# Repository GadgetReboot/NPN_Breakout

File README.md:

# NPN_Breakout
NPN Transistor Breakout Board

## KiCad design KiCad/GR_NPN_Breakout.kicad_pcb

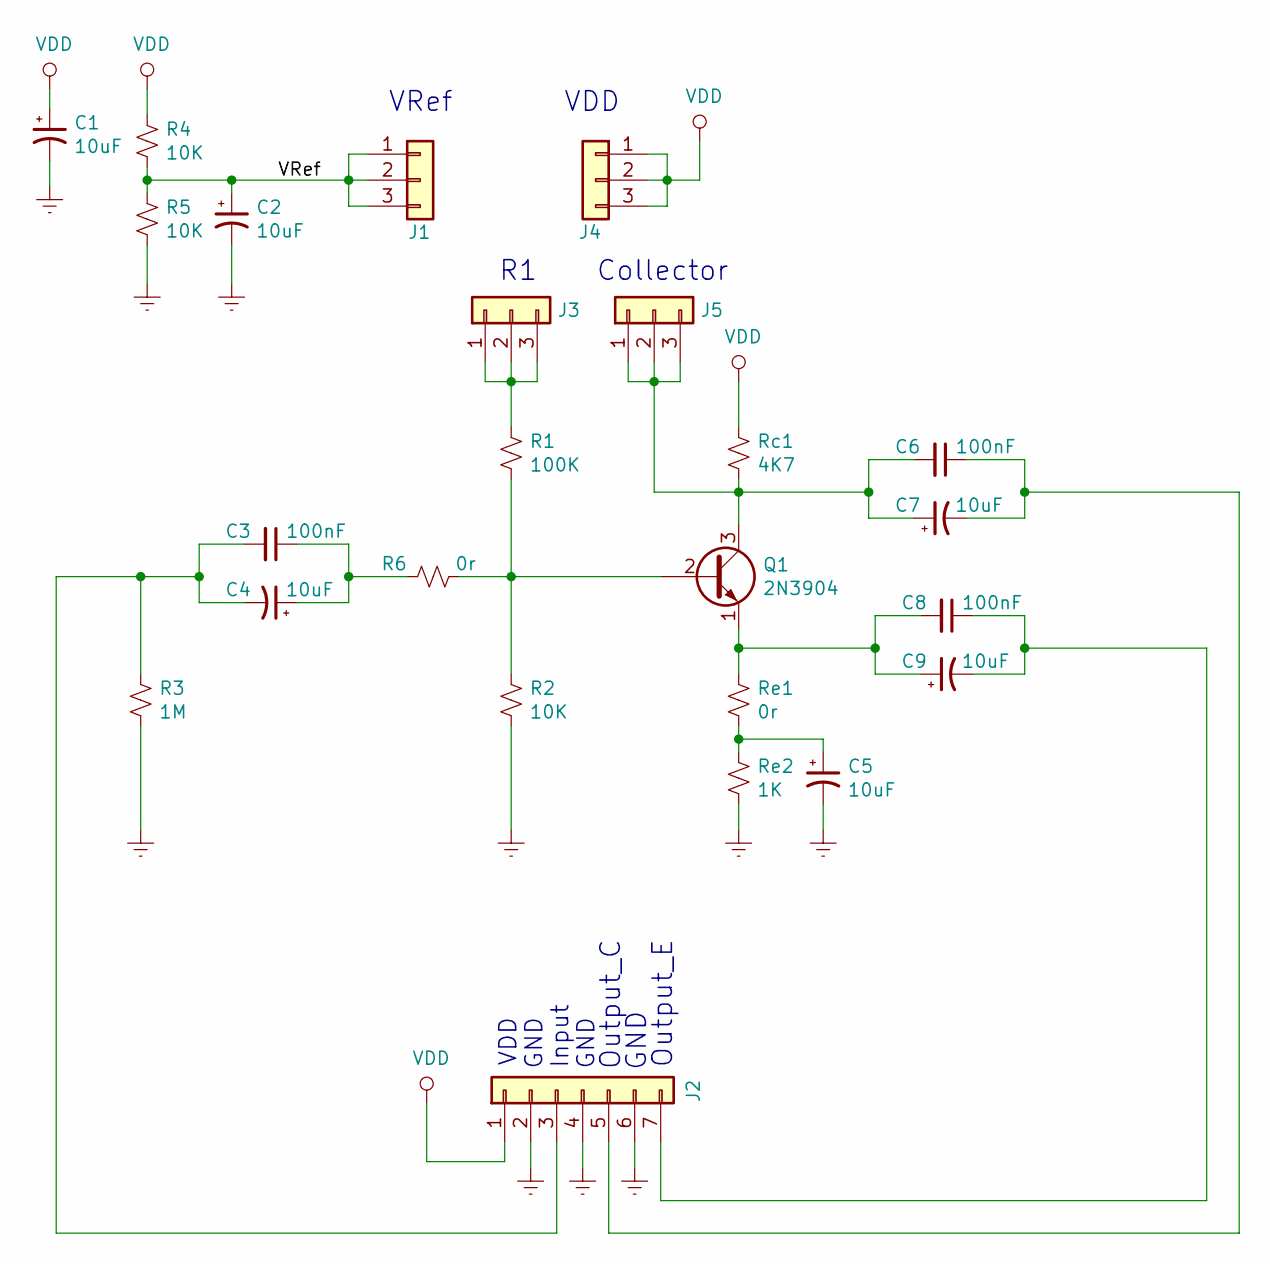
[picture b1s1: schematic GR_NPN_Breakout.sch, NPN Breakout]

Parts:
C1, C2, C4, C5, C7, C9: 10uF; CP_Radial_D5.0mm_P2.50mm
C3, C6, C8: 100nF; C_Disc_D3.0mm_W1.6mm_P2.50mm
J1, J3, J4, J5: Conn_01x03; PinHeader_1x03_P2.54mm_Vertical
J2: Conn_01x07; PinHeader_1x07_P2.54mm_Vertical
Q1: 2N3904; TO-92_Inline_Wide
R1: 100K; R_Axial_DIN0207_L6.3mm_D2.5mm_P10.16mm_Horizontal
R2, R4, R5: 10K; R_Axial_DIN0207_L6.3mm_D2.5mm_P10.16mm_Horizontal
R3: 1M; R_Axial_DIN0207_L6.3mm_D2.5mm_P10.16mm_Horizontal
R6: 0r; R_Axial_DIN0207_L6.3mm_D2.5mm_P10.16mm_Horizontal
Rc1: 4K7; R_Axial_DIN0207_L6.3mm_D2.5mm_P10.16mm_Horizontal
Re1: 0r; R_Axial_DIN0207_L6.3mm_D2.5mm_P10.16mm_Horizontal
Re2: 1K; R_Axial_DIN0207_L6.3mm_D2.5mm_P10.16mm_Horizontal

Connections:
/VRef: C2.1, J1.1, J1.2, J1.3, R4.2, R5.1
GNDREF: C1.2, C2.2, C5.2, J2.2, J2.4, J2.6, R2.2, R3.2, R5.2, Re2.2
unnamed: C3.1, C4.1, R6.2
unnamed: C3.2, C4.2, J2.3, R3.1
unnamed: C5.1, Re1.2, Re2.1
unnamed: C6.1, C7.2, J2.5
unnamed: C6.2, C7.1, J5.1, J5.2, J5.3, Q1.3 (C), Rc1.2
unnamed: C8.1, C9.2, J2.7
unnamed: C8.2, C9.1, Q1.1 (E), Re1.1
unnamed: J3.1, J3.2, J3.3, R1.1
unnamed: Q1.2 (B), R1.2, R2.1, R6.1
VDD: C1.1, J2.1, J4.1, J4.2, J4.3, R4.1, Rc1.1

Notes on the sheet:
Output_C
GND
VDD
Input
Output_E
VRef
Collector

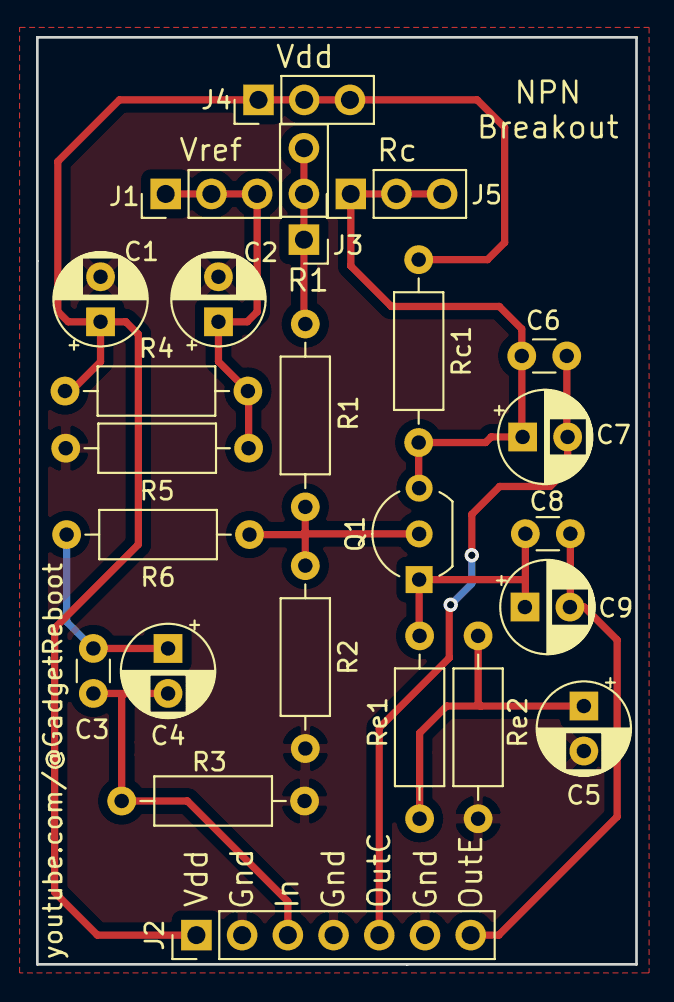
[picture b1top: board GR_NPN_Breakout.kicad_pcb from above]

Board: 2 copper layers, 33.3 x 51.5 mm, 24 parts (0 on the bottom side), 12 nets.
